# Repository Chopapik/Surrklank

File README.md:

# Surrklank

Surrklank is a local application for an ESP32 device. ASP.NET Core serves the
React interface and communicates with the ESP32 over BLE. The firmware currently
supports connection, ATX control, an FDD Laboratory for up to 12 drives (three FDD modules) and USB/BLE
firmware maintenance. Laboratory motion has been exercised on two physical
FDDs; see the [firmware limits](docs/FIRMWARE.md#fdd-laboratory).

The wiring reference uses **LSM (Lead-Screw Motor)** for the removed optical-drive
stepper motors with lead screws, alongside FDD and HDD. LSM/HDD playback remains
unimplemented; see [instrument names](docs/WIRING.md#instrument-names).

## Run

Install the .NET 10 SDK, Node.js 24 or newer, npm and PlatformIO Core. Build the
frontend before starting ASP.NET:

```sh
npm --prefix frontend ci
npm --prefix frontend run build
python3 run.py
```

On Windows, use `py run.py`. Open <http://127.0.0.1:5173>. `run.py` launches the
C# application; ASP.NET serves `frontend/dist` in the same process. Rider can
also run `backend/Surrklank.csproj` directly. Rebuild the frontend when serving
changed UI files through ASP.NET.

For frontend development, keep ASP.NET running, start
`npm --prefix frontend run dev`, and open <http://127.0.0.1:5174>. Vite forwards
`/api` and `/ws` to ASP.NET. `frontend/dist` and `node_modules` are generated.

The backend uses SimpleSharpBLE 1.2.0. Its packaged native libraries support
Apple Silicon macOS, Windows x64/ARM64 and Linux x64/ARM64, but not Intel macOS.
macOS needs Bluetooth permission for the application or terminal running the
server; Linux needs BlueZ and D-Bus. Check the library's Business Source License
1.1 before commercial use. The first .NET restore needs NuGet access.

## Use the device

The ESP32 advertises the compatibility name `EM-MIDI-IDF`. The application scans
and connects automatically, including after link loss. **Disconnect** pauses
automatic connection until **Connect** is selected. **Ping** is manual; there is
no heartbeat. Browser connection and firmware status arrive over `/ws`.

The ATX switch requests an explicit ON or OFF state. GPIO19 drives the transistor
and the physical GPIO13 button can also change the request. The displayed state
comes from the ESP32's driven output, not from browser storage or a measured
power rail. An unknown state disables the switch. See [wiring](docs/WIRING.md).
ATX ON needs the remote panel connected when the ESP32 starts; otherwise the
app shows that the panel is not connected or not responding. The panel's STOP
button stops every drive even without the app.
The ATX section also shows PWR_OK, the supply's own rail-good signal, and
alerts while ATX is ON without it; the modules stay disconnected until PWR_OK
returns. It lists each actuator module as responding, not responding or
reporting a DRV8833 fault (over-current or over-temperature, not a missing
motor).

**Linie SELECT napędów** sets the select line of each FDD: DS1 for typical PC
drives, DS0 for Amiga drives. The ESP32 stores it and the fields are disabled
while anything plays. The bring-up chain test has no UI control; see
[FIRMWARE.md](docs/FIRMWARE.md#bring-up-chain-test).

The FDD Laboratory selects one or several drives, frequency and playing time.
A batch starts only after every selected drive passes its TRACK0 check.
At 200 Hz and above, the high-rate firmware profile ramps once at tone start
and allows a longer direction-change pause. The mean step rate over the whole
tone is lower than the setting. See the [motion profile](docs/FIRMWARE.md#fdd-laboratory)
when interpreting measurements.
Separate batches can overlap; **Stop FDD** stops one drive and **Stop all**
stops all drives, including preparation. Both finish by parking at TRACK0.
When duration expires, the head stays in place (`stopped`). The next start homes
and checks it before playing again. Live states and telemetry arrive over the
same `/ws`. Stop and wait for parking
before switching ATX off or uploading firmware. The physical ATX button is
ignored while Laboratory owns the drives.

Timing-capable firmware also retains a bounded FDD event history with ESP32
monotonic timestamps. Integrations can query clock correspondence and replay
history through the [timing API](docs/BLE-PROTOCOL.md#laboratory-timing-v1).
Timestamp precision is not independently validated synchronization accuracy.

## Firmware maintenance

Isolate the ESP32 before an upload: USB only, with ATX and register/instrument
wiring disconnected. The interface asks for this confirmation. USB provisioning
requires selecting the connected CP2102 port; BLE OTA transfers only the
application image. The application builds from the current `firmware/` sources.
Neither mode changes eFuses or flash security settings.

Maintenance blocks conflicting device controls. An upload request returns HTTP
202 when the job starts; completion or failure is reported over `/ws`. A busy
device returns HTTP 409 with a reason. If the flash outcome cannot be confirmed,
the job is `uncertain` and does not resend the image automatically. Closing the
browser does not cancel an upload. See [firmware operation](docs/FIRMWARE.md).

## Interfaces and checks

| Interface | Purpose |
| --- | --- |
| `GET /` | React interface |
| `GET /api/connection` | Current connection and firmware snapshot |
| `GET /api/connection/events?limit=10` | Recent connection events |
| `PUT /api/atx` | Explicit `{"state":"on"}` or `{"state":"off"}` request |
| `POST /api/laboratory/play` | Prepare and start a `devices` batch |
| `POST /api/laboratory/stop` | Stop and park one FDD |
| `POST /api/laboratory/stop/all` | Stop and park all FDDs |
| `GET /api/firmware/ports` | Available CP2102 ports |
| `POST /api/firmware/usb`, `POST /api/firmware/ota` | Start a firmware job |
| `WS /ws` | `state` / `laboratory` snapshots and connection actions |

Firmware requests require `{"isolatedHardwareConfirmed":true}`; USB also needs
`"port":"<selected CP2102 port>"`. Local-origin checks apply to mutating HTTP
requests and browser WebSockets. See [application architecture](docs/ARCHITECTURE.md)
and [BLE application protocol](docs/BLE-PROTOCOL.md) for the state flow.

Offline checks:

```sh
dotnet build backend/Surrklank.csproj
npm --prefix frontend run build
npm --prefix frontend test
python3 backend/checks/test_device_state.py
python3 firmware/tests/test_atx_power.py
python3 firmware/tests/test_fdd.py
pio run -d firmware -e esp32
```

The backend check compiles the production state decoder in a temporary .NET
harness; the ATX check compiles the production C++ module with GPIO/FreeRTOS
stubs. The FDD check exercises the production scheduling engine with simulated
TRACK0 and movement, including unequal outward/return movement. These checks
and builds do not exercise a physical ESP32. No C# test
suite for the orchestration layer is included.

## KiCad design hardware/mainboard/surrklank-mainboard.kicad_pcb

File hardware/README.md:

# Surrklank PCB design

Status: **proposed design, not built or tested.** Signals, pins, pull
resistors and power wiring of the planned boards are defined in
[WIRING.md](../docs/WIRING.md); this file covers board-level design only.
Firmware drives three FDD modules (12 drives) and keeps the actuator branch cleared; see
[FIRMWARE.md](../docs/FIRMWARE.md#fdd-laboratory).

KiCad 10 projects:

| Folder | Content |
| --- | --- |
| `fdd-module/` | FDD module v0.1: generated schematic and autorouted 100 × 80 mm 2-layer PCB |
| `actuator-module/` | actuator module v0.1: generated schematic and autorouted 120 × 80 mm 2-layer PCB |
| `mainboard/` | Mainboard v0.1: generated schematic and autorouted 100 × 80 mm 2-layer PCB (within the 100 × 100 mm low-cost fab class) |
| `panel/` | Remote panel v0.1: generated schematic and autorouted 100 × 59 mm 2-layer PCB |
| `surrklank-controller/` | Empty first KiCad project, superseded by `mainboard/` |
| `lib/` | Custom symbols (DRV8833 module, ESP32 38-pin board) and footprints (KF301 screw terminals, ESP32 board, DRV8833 module, Surrklank logo) |
| `tools/` | Generators, netlist check and build script |

Boards are generated, not edited by hand. One command rebuilds a board
(schematic, ERC, netlist check, placement, autorouting, zone fill, DRC with
schematic parity and all severities):

```sh
hardware/tools/build_fdd_module.sh [work_dir]
hardware/tools/build_actuator_module.sh [work_dir]
hardware/tools/build_mainboard.sh [work_dir]
hardware/tools/build_panel.sh [work_dir]
```

All wrap `build_module.sh fdd|actuator|mainboard|panel`, which stops at the first
failing step. Placement, zones and branding of all boards live in
`gen_module_pcb.py`.

Requirements: KiCad 10 (its bundled Python runs `gen_module_pcb.py`), Freerouting
2.5.0 jar in `~/.local/share/freerouting/bin/` (official GitHub release,
SHA-256 `f6f51bb0…5de3c7`) and Java 25 (`brew install openjdk@25`). The script
runs Freerouting headless with analytics and telemetry disabled. The native
Freerouting 2.5.0 CLI build fails on board serialization and is not used.

- `check_fdd_module.py`, `check_actuator_module.py`, `check_mainboard.py` and
  `check_panel.py` verify the netlist against WIRING.md rules written
  independently of the generator (drive header pins, pull-ups, register chain,
  ribbon, supplies).
- Routing is not deterministic: each run gives different tracks, and a run
  occasionally leaves a connection unrouted; rerun the build then. The build
  passes only with zero DRC violations and zero unconnected pads.
- Design rules: Default class 0.25 mm tracks / 0.2 mm clearance, Power class
  (+5V, +3V3, GND) 0.6 mm / 0.25 mm, vias 0.6/0.3 mm, minimum track 0.15 mm
  (above the 0.127 mm limit of low-cost fabs). Freerouting neck-down is disabled;
  any remaining track under 0.15 mm is widened and re-checked by DRC.
- GND is poured on both layers with solid pad connections; dense IDE header
  pins left no room for thermal spokes.
- Actuator module load supply: a +5V band on B_Cu (7.9 mm at its widest, 4.7 mm at the
  four GND notches, about 10 A at +20 K for 1 oz copper by an IPC-2221 estimate;
  the terminal and the PSU wire limit first, so consider 2 oz copper) runs from the two +5V
  poles of KF301 J5 past C8 (+) and the VCC pins of all four DRV8833 slots. Below it
  B_Cu is a solid GND plane reaching each slot's GND pin through a notch in the
  band, plus the two GND poles of J5 and C8 (−). Both zones are passed to Freerouting
  as planes, and a rule area forbids B_Cu tracks and vias there, so signals
  cross on F_Cu only. The band's current capacity for the theoretical 9.6 A is
  estimated, not calculated or measured; the LDO is fed by a 0.6 mm track.
- The autorouted layout is electrically complete but not hand-optimised
  (long detours, signals near edges). It has not been reviewed for signal
  integrity or checked with a 1:1 paper print.

## Board family

| Board | Contents |
| --- | --- |
| Mainboard | ESP32 board, ATX switch and button, PWR_OK input, 5VSB supply, one ribbon connector per branch, remote panel connector |
| FDD module | 3 × 74HC595, 1 × 74HC165, input buffer, LDO, two 40-pin IDE headers, IN/OUT ribbon connectors, one 2-pole KF301 |
| actuator module | Four DRV8833 module positions, 3 × 74HC595, 1 × 74HC165, input buffer, LDO, IN/OUT ribbon connectors, one 4-pole KF301 |

At least two module designs are needed. Whether the mainboard is a third design
or is merged into one of them is not decided.

## Mainboard

ESP32 board as purchased: "ESP32-WROOM-32 38-pin, micro-USB, CP2102"
(seller code ARD-ESP32-38P), about 55.3 × 28 mm, 2 × 19 pins on 2.54 mm pitch,
pin order listed by the seller and matching the silkscreen photo.

- Row spacing is **24.85 mm** centre to centre (many official DevKitC boards
  and 38-pin clones differ: 25.4 and 22.86 mm also occur). Measured by the user
  with a caliper: 25.5 mm across the rows on pin outer edges (minus the 0.64 mm
  pin width) and 24.8 to 24.9 mm directly centre to centre; along a row 46.0 mm
  across 18 pitches (45.72 mm nominal). An earlier footprint used 25.4 mm and
  did not fit a paper dry fit.
- The board plugs into two 1 × 19 female headers on the left of the PCB. Its
  antenna end is flush with the top edge and the top 3.6 mm under it carries
  no copper on either layer (Surrklank uses BLE). It does not overhang: the
  body outline in the footprint is approximate, so the antenna position on
  the real board is not checked.
- Below the USB end the PCB is left free (only the silkscreen note
  "REMOVE JP1 BEFORE USB") so the micro-USB plug clears the ATX terminal (KF301 J1, x 37-58 mm, y 66-74 mm).
- PCB v0.1 layout: register control resistor arrays in the middle, ribbon
  J2 (FDD) and J3 (actuator module) on the right edge, ATX terminal J1 (KF301, 4 poles) at the bottom
  edge with the wire entry outward and labelled poles above it, button J4 bottom right, remote panel
  connector J6 (2 × 5 IDC, see WIRING.md) at the top edge. Autorouted, not
  hand-optimised.
- Power input: KF301 screw terminal on every board that takes power (mainboard 4 poles,
  FDD module 2, actuator module 4); ATX button on a two-pin connector.

## Remote panel

Front panel on a cable to mainboard J6 (pinout in WIRING.md). PCB v0.1,
everything on the front side:

- J1 cable header top left; socket J4 for a 0.96" SSD1306 OLED module (the
  module's 27 × 27 mm body covers the area below the socket, which carries
  only tracks); four 3 mm LEDs top right: STBY and RAILS (hardware), ATX ON
  and ESP (firmware via the expander).
- MCP23017 expander (address 0x20) with 330 Ω LED resistors; 6 mm tactile
  buttons POWER (straight to GPIO13), PREV, PLAY, STOP, NEXT (expander GPA0–3).
- J2 (JST-XH 6-pin): +3V3, GND and GPA4–GPA7 (GPA7 is output only, so three
  more buttons); J3
  (JST-XH 4-pin): I2C extension (GND, VCC, SCL, SDA) for another expander or
  sensor. Keyed JST-XH as on the actuator module outputs, at the bottom edge. GPB2–GPB7 are unused: routing
  them to a header blocked the autorouter.
- All panel nets use the Default 0.25 mm class; the panel draws tens of mA
  and GND is poured on both layers. With 0.6 mm Power tracks Freerouting
  could not route GND between the expander and header pins and left +3V3
  unrouted as well.
- Not decided: mounting in an enclosure, front-panel cutouts, LED colours
  (Vf about 2 V needed for the hardware LEDs).

## Connectors and footprints

| Part | Footprint |
| --- | --- |
| Ribbon IN/OUT | 2 × 8 IDC box header, 2.54 mm |
| FDD drive cable | Salvaged 40-pin IDE header; standard DIN 41651 2 × 20 footprint (2.54 mm pitch, 1.0 mm holes, body about 58.5 × 8.9 mm in KiCad) with extra clearance for a cut-down housing |
| Power input | Custom `TerminalBlock_KF301_1xNN_P5.08mm_Horizontal` (2 and 4 poles, from `gen_terminal_footprints.py`): 5.08 mm pitch, 3.0 mm pads, 1.4 mm holes, generic body about 8 mm deep with the wires entering from the +y side; check against the bought part |
| DRV8833 module | Custom `DRV8833_Module_2x6_W15.24mm`: 2 × 6, 2.54 mm pitch, rows 15.24 mm apart, 1.0 mm holes, DIP-style numbering |
| Motor outputs | JST-XH 4-pin vertical (B4B-XH-A, 2.5 mm) per DRV8833 slot; crimped plugs |
| Actuator module bulk capacitor | 470 µF 16 V radial THT, 10 mm diameter, 5 mm pitch |
| ESP32 board | Two 1 × 19 female headers, 2.54 mm pitch, rows 24.85 mm apart |

Salvaged male Molex headers turned out to be SMD, so every power input is a
KF301 screw terminal (see WIRING.md, Power). A cut-off IDE part can still serve
as an FDD module header.

## Layout notes

- Silkscreen branding, white, board-only footprints (not in the schematic):
  the Surrklank mark (10 mm frame with the beamed-notes glyph, 55 % of the frame
  height, footprint `Surrklank_Mark_10mm` from `gen_logo_footprints.py`) with the
  wordmark "Surrklank" and the board name and revision below it, and the author
  mark (8 mm square ring, `Surrklank_Logo_8mm`) with a small italic "by" in its
  upper-left corner. The author mark is on the back of every board, the front
  carries only the Surrklank mark.
  `gen_module_pcb.py <board> brand` re-applies them without rerouting. Wordmark
  and "by" are TrueType text (Arial bold, Georgia bold italic) outlined in the
  Gerbers; a different font on another machine changes their shape.
- actuator module: ribbon IN/OUT on the left and right edges, registers in a
  row above four DRV8833 slots (rotated so OUT1–OUT4 face the bottom edge),
  JST-XH motor connectors at the bottom edge, 4-pole KF301 J5 at the left edge
  with C8 beside it. Every pole is labelled with its function (+5V or GND) to
  the right of the terminal body. The board is 120 mm wide: C8 and four 18.6 mm
  slots do not fit in 100 mm.
- Ribbon signals keep the signal/ground order of the 16-pin assignment.
- Both modules carry bring-up aids: LEDs D1-D5 (register serial outputs, 165
  return, 3.3 V) at the registers and header J11 (3V3, DATA, CLK, LATCH, end of
  chain, GND). The FDD module stays 100 x 80 mm, within the 100 x 100 mm limit.

## Manufacturing

There is no factory assembly: bare boards are ordered and every part is bought
separately and soldered by hand (SOIC, 0603 and SOT-223 included). The BOM
written by `export_jlcpcb.py` doubles as a shopping list.

`hardware/tools/export_review.py [board ...]` writes review tables to
`hardware/fabrication/review/` (git-ignored): a pin-by-pin table per board from
the netlist (connectors, modules, switches, LEDs: pin name, net, what else is
on it). The tables are generated from the schematic, so they are the thing to
compare with the real parts and breadboard wiring; `check_*.py` only compares
the schematic with WIRING.md.

`hardware/tools/export_dryfit.py` (run with KiCad's Python, which provides
`pcbnew`) writes `surrklank-dryfit-a4-1to1.pdf` to the same folder: one A4
landscape sheet with all four boards at true size for a paper dry fit. Black
lines are the board edge, footprint outlines and mounting holes; red circles
are through-hole pads with their drills; tracks and SMD parts are left out to
save ink. A 10 cm ruler along both axes shows whether the printer rescaled the
page: print at 100 % / actual size, never fit to page.

`hardware/tools/export_jlcpcb.py [board ...]` writes upload files to
`hardware/fabrication/` (git-ignored): one Gerber and drill zip per board
(separate PTH and NPTH files, paste layers included), plus an SMD BOM (`bom/`) and CPL (`cpl/`)
that are only needed if factory assembly is used. The BOM carries only
LCSC numbers whose JLCPCB class was read as Basic or Promotional (Preferred)
Extended on 2026-11-15 (class and stock change, recheck before ordering);
the only Promotional part is the 74HC165 (C5613), which is free of the
loading fee in Economic assembly only. Four part types have no Basic or
Promotional option and stay without a number, listed in `UNRESOLVED` in the
script with their Extended candidates (extra fee per unique part type):
74LVC244A (SOIC-20W) on both modules, the 33 Ω 0603 × 4 array (mainboard and
both modules), the 100 k 0603 × 4 array (actuator module) and the panel's
MCP23017-E/SO. These parts are left out of the assembly BOM and CPL and listed
in `bom/surrklank-<board>-hand-solder.csv`: the factory places only Basic and
Promotional parts and these are soldered by hand. CPL rotation offsets are verified only for
SOIC-16/20 and SOT-223; SOT-23, resistor arrays and SOIC-28W must be checked
in the JLCPCB placement preview.

## Open items

- Before ordering: dry-fit the 1:1 sheet (`export_dryfit.py`) with the real ESP32
  board, salvaged IDE header, KF301 terminals, buttons and OLED; measure the
  DRV8833 module J1 and EEP pull-up supply with a multimeter.
- Parts: AMS1117 with the 22 µF 1206 ceramic is untested (datasheet silent on
  ceramics; scope the 3.3 V rail of the first module).
- Power input: KF301 pole and body size against the bought terminals (generic values in the footprints).
- MOTOR behaviour on the installed drives (the hand-wired assembly works with
  TRACK0 pulled up and no 595 output pull-ups).
- Motor supply current per actuator module and wire gauge.
- Firmware migration after assembly: six outputs per drive and a longer FDD
  chain (48 output bits for two modules), 165 chains with WRITE PROTECT and
  FAULT bits, configurable select line, EEP control, PWR_OK input on GPIO36,
  actuator Q165 on GPIO35, DATA, CLK, LATCH and CLK165 held LOW (and /OE and
  /PL HIGH) while ATX is off.

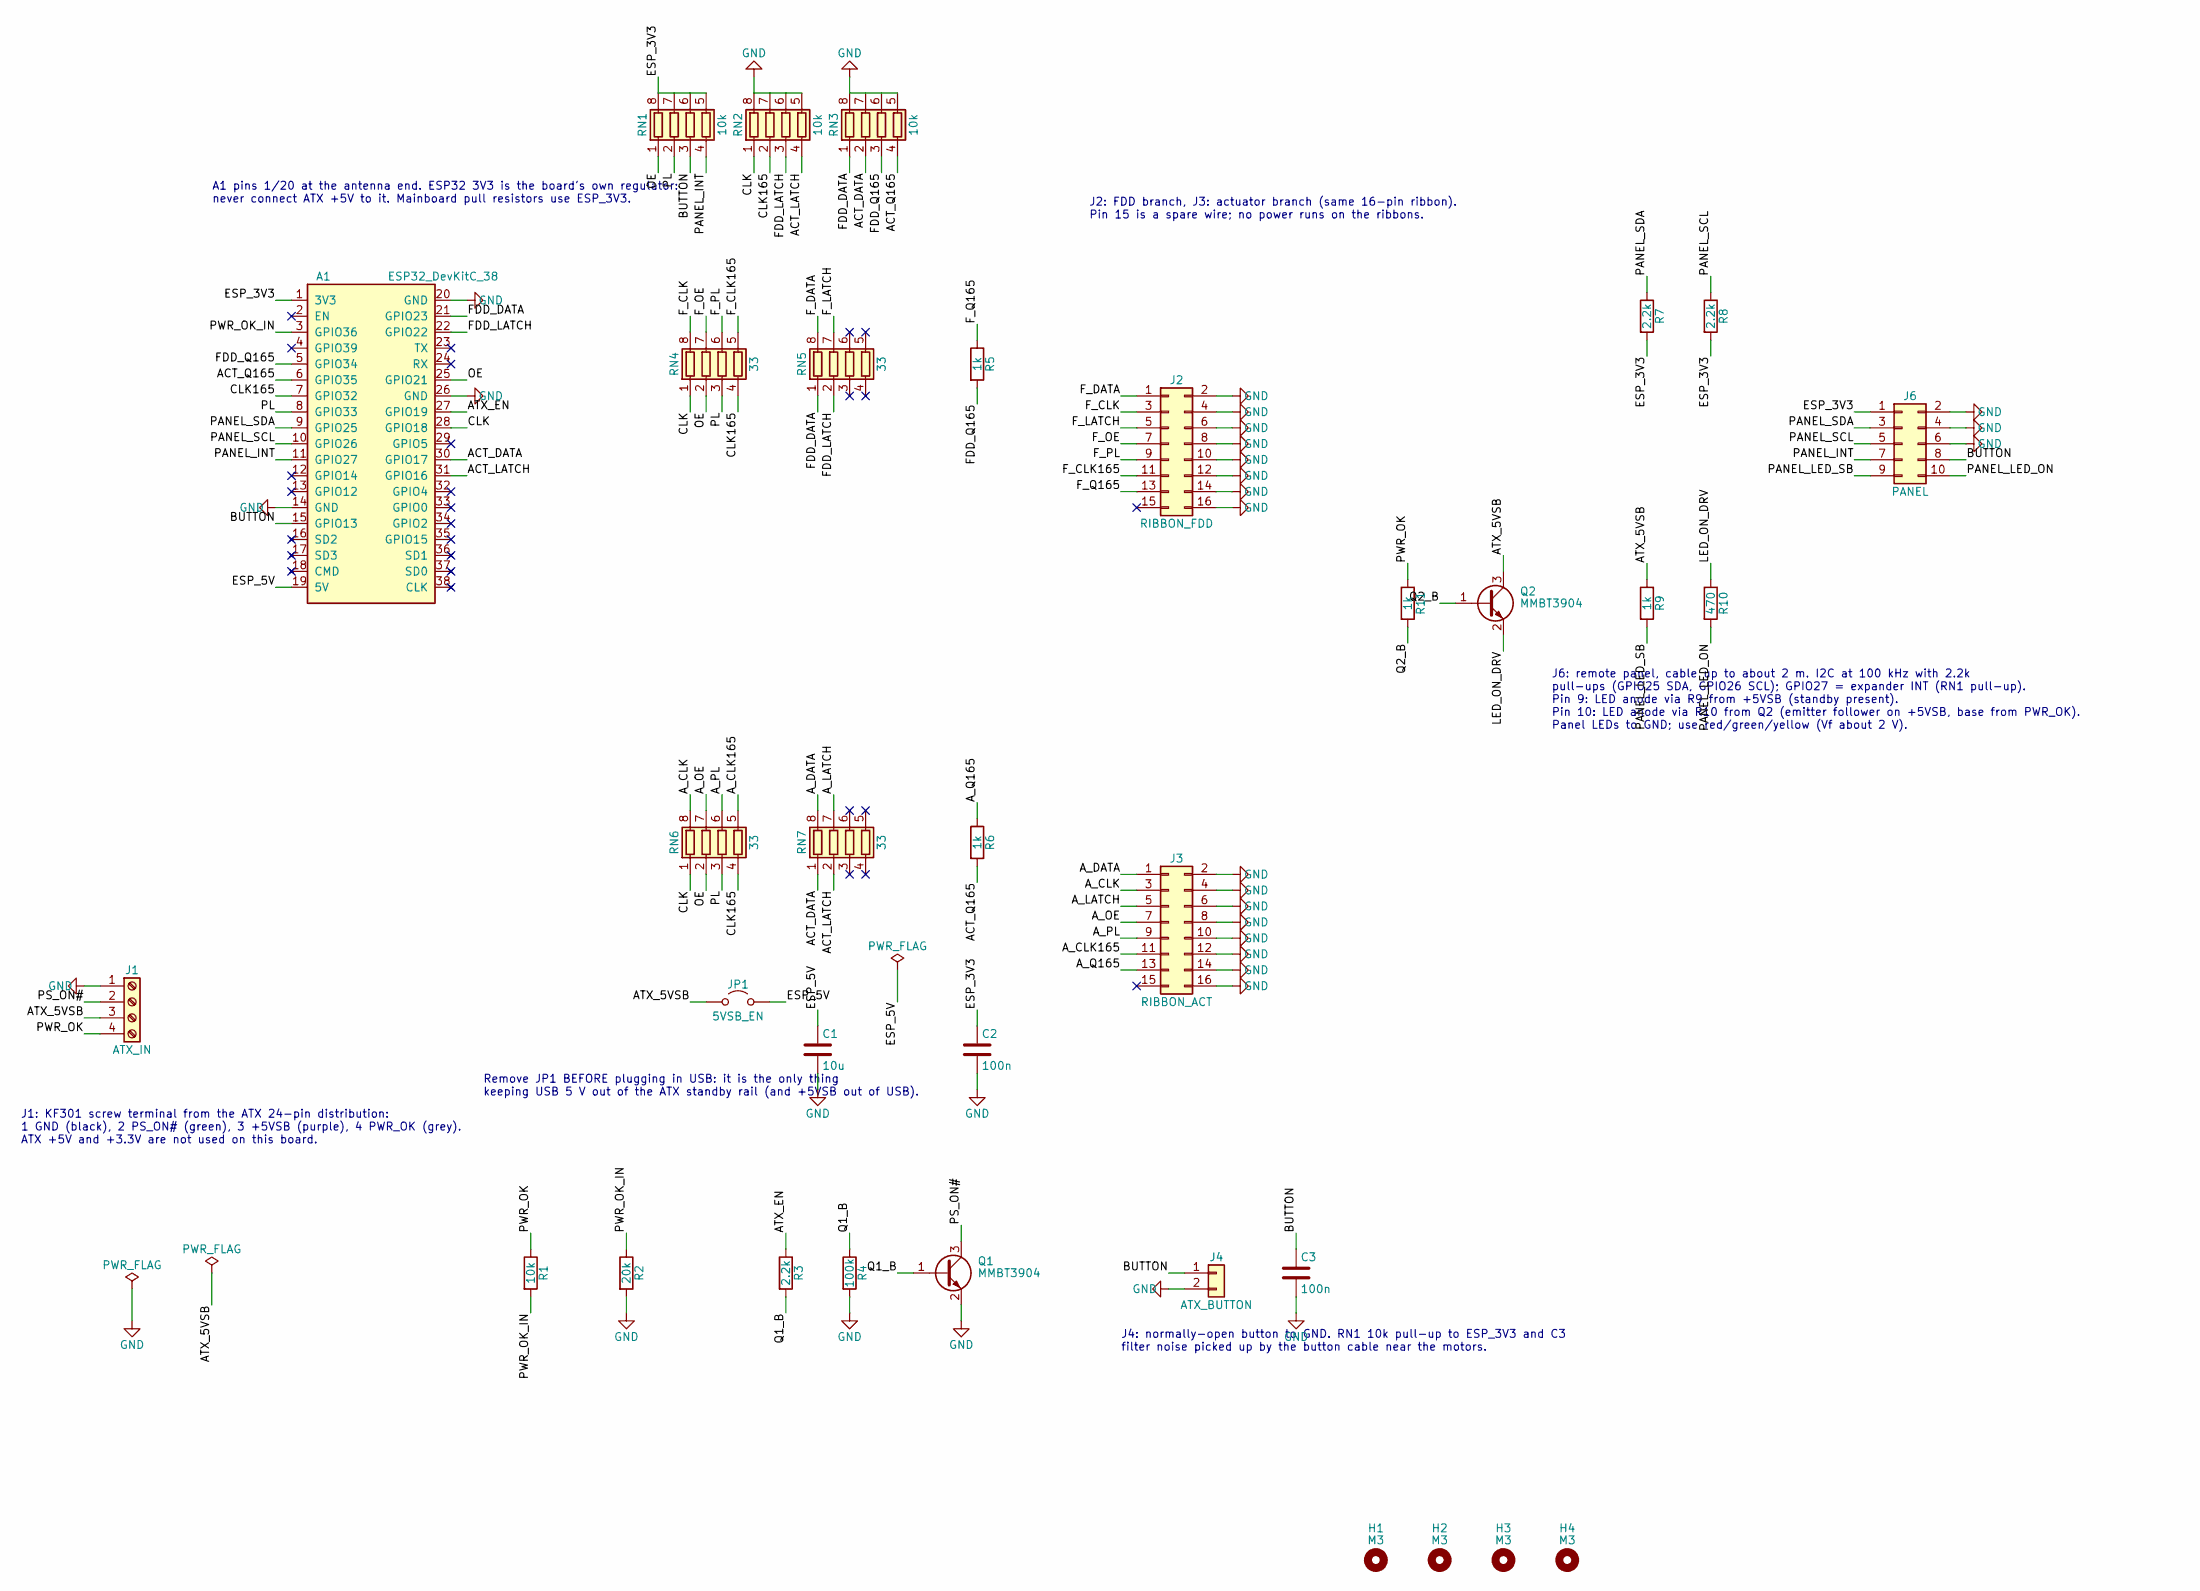
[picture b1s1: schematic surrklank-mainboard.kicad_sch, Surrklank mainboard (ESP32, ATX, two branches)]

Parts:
A1: ESP32_DevKitC_38; ESP32_DevKitC_38_W24.85mm
C1: 10u; C_0805_2012Metric
C2, C3: 100n; C_0805_2012Metric
H1, H2, H3, H4: M3; MountingHole_3.2mm_M3
J1: ATX_IN; TerminalBlock_KF301_1x04_P5.08mm_Horizontal
J2: RIBBON_FDD; IDC-Header_2x08_P2.54mm_Vertical
J3: RIBBON_ACT; IDC-Header_2x08_P2.54mm_Vertical
J4: ATX_BUTTON; JST_XH_B2B-XH-A_1x02_P2.50mm_Vertical
J6: PANEL; IDC-Header_2x05_P2.54mm_Vertical
JP1: 5VSB_EN; PinHeader_1x02_P2.54mm_Vertical
Q1, Q2: MMBT3904; SOT-23
R1: 10k; R_0805_2012Metric
R2: 20k; R_0805_2012Metric
R3, R7, R8: 2.2k; R_0805_2012Metric
R4: 100k; R_0805_2012Metric
R5, R6, R9, R11: 1k; R_0805_2012Metric
R10: 470; R_0805_2012Metric
RN1, RN2, RN3: 10k; R_Array_Convex_4x0603
RN4, RN5, RN6, RN7: 33; R_Array_Convex_4x0603

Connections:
/ACT_DATA: A1.30 (GPIO17), RN3.2 (R2.1), RN7.1 (R1.1)
/ACT_LATCH: A1.31 (GPIO16), RN2.4 (R4.1), RN7.2 (R2.1)
/ACT_Q165: A1.6 (GPIO35), R6.2, RN3.4 (R4.1)
/ATX_5VSB: J1.3, JP1.1 (A), Q2.3 (C), R9.1
/ATX_EN: A1.27 (GPIO19), R3.1
/A_CLK: J3.3, RN6.8 (R1.2)
/A_CLK165: J3.11, RN6.5 (R4.2)
/A_DATA: J3.1, RN7.8 (R1.2)
/A_LATCH: J3.5, RN7.7 (R2.2)
/A_OE: J3.7, RN6.7 (R2.2)
/A_PL: J3.9, RN6.6 (R3.2)
/A_Q165: J3.13, R6.1
/BUTTON: A1.15 (GPIO13), C3.1, J4.1, J6.8, RN1.3 (R3.1)
/CLK: A1.28 (GPIO18), RN2.1 (R1.1), RN4.1 (R1.1), RN6.1 (R1.1)
/CLK165: A1.7 (GPIO32), RN2.2 (R2.1), RN4.4 (R4.1), RN6.4 (R4.1)
/ESP_3V3: A1.1 (3V3), C2.1, J6.1, R7.2, R8.2, RN1.5 (R4.2), RN1.6 (R3.2), RN1.7 (R2.2), RN1.8 (R1.2)
/ESP_5V: A1.19 (5V), C1.1, JP1.2 (B)
/FDD_DATA: A1.21 (GPIO23), RN3.1 (R1.1), RN5.1 (R1.1)
/FDD_LATCH: A1.22 (GPIO22), RN2.3 (R3.1), RN5.2 (R2.1)
/FDD_Q165: A1.5 (GPIO34), R5.2, RN3.3 (R3.1)
/F_CLK: J2.3, RN4.8 (R1.2)
/F_CLK165: J2.11, RN4.5 (R4.2)
/F_DATA: J2.1, RN5.8 (R1.2)
/F_LATCH: J2.5, RN5.7 (R2.2)
/F_OE: J2.7, RN4.7 (R2.2)
/F_PL: J2.9, RN4.6 (R3.2)
/F_Q165: J2.13, R5.1
/LED_ON_DRV: Q2.2 (E), R10.1
/OE: A1.25 (GPIO21), RN1.1 (R1.1), RN4.2 (R2.1), RN6.2 (R2.1)
/PANEL_INT: A1.11 (GPIO27), J6.7, RN1.4 (R4.1)
/PANEL_LED_ON: J6.10, R10.2
/PANEL_LED_SB: J6.9, R9.2
/PANEL_SCL: A1.10 (GPIO26), J6.5, R8.1
/PANEL_SDA: A1.9 (GPIO25), J6.3, R7.1
/PL: A1.8 (GPIO33), RN1.2 (R2.1), RN4.3 (R3.1), RN6.3 (R3.1)
/PS_ON#: J1.2, Q1.3 (C)
/PWR_OK: J1.4, R1.1, R11.1
/PWR_OK_IN: A1.3 (GPIO36), R1.2, R2.1
/Q1_B: Q1.1 (B), R3.2, R4.1
/Q2_B: Q2.1 (B), R11.2
GND: A1.14 (GND), A1.20 (GND), A1.26 (GND), C1.2, C2.2, C3.2, J1.1, J2.2, J2.4, J2.6, J2.8, J2.10, J2.12, J2.14, J2.16, J3.2, J3.4, J3.6, J3.8, J3.10, J3.12, J3.14, J3.16, J4.2, J6.2, J6.4, J6.6, Q1.2 (E), R2.2, R4.2, RN2.5 (R4.2), RN2.6 (R3.2), RN2.7 (R2.2), RN2.8 (R1.2), RN3.5 (R4.2), RN3.6 (R3.2), RN3.7 (R2.2), RN3.8 (R1.2)

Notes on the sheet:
A1 pins 1/20 at the antenna end. ESP32 3V3 is the board's own regulator: never connect ATX +5V to it. Mainboard pull resistors use ESP_3V3.
J2: FDD branch, J3: actuator branch (same 16-pin ribbon). Pin 15 is a spare wire; no power runs on the ribbons.
J1: KF301 screw terminal from the ATX 24-pin distribution: 1 GND (black), 2 PS_ON# (green), 3 +5VSB (purple), 4 PWR_OK (grey). ATX +5V and +3.3V are not used on this board.
Remove JP1 BEFORE plugging in USB: it is the only thing keeping USB 5 V out of the ATX standby rail (and +5VSB out of USB).
J4: normally-open button to GND. RN1 10k pull-up to ESP_3V3 and C3 filter noise picked up by the button cable near the motors.
J6: remote panel, cable up to about 2 m. I2C at 100 kHz with 2.2k pull-ups (GPIO25 SDA, GPIO26 SCL); GPIO27 = expander INT (RN1 pull-up). Pin 9: LED anode via R9 from +5VSB (standby present). Pin 10: LED anode via R10 from Q2 (emitter follower on +5VSB, base from PWR_OK). Panel LEDs to GND; use red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

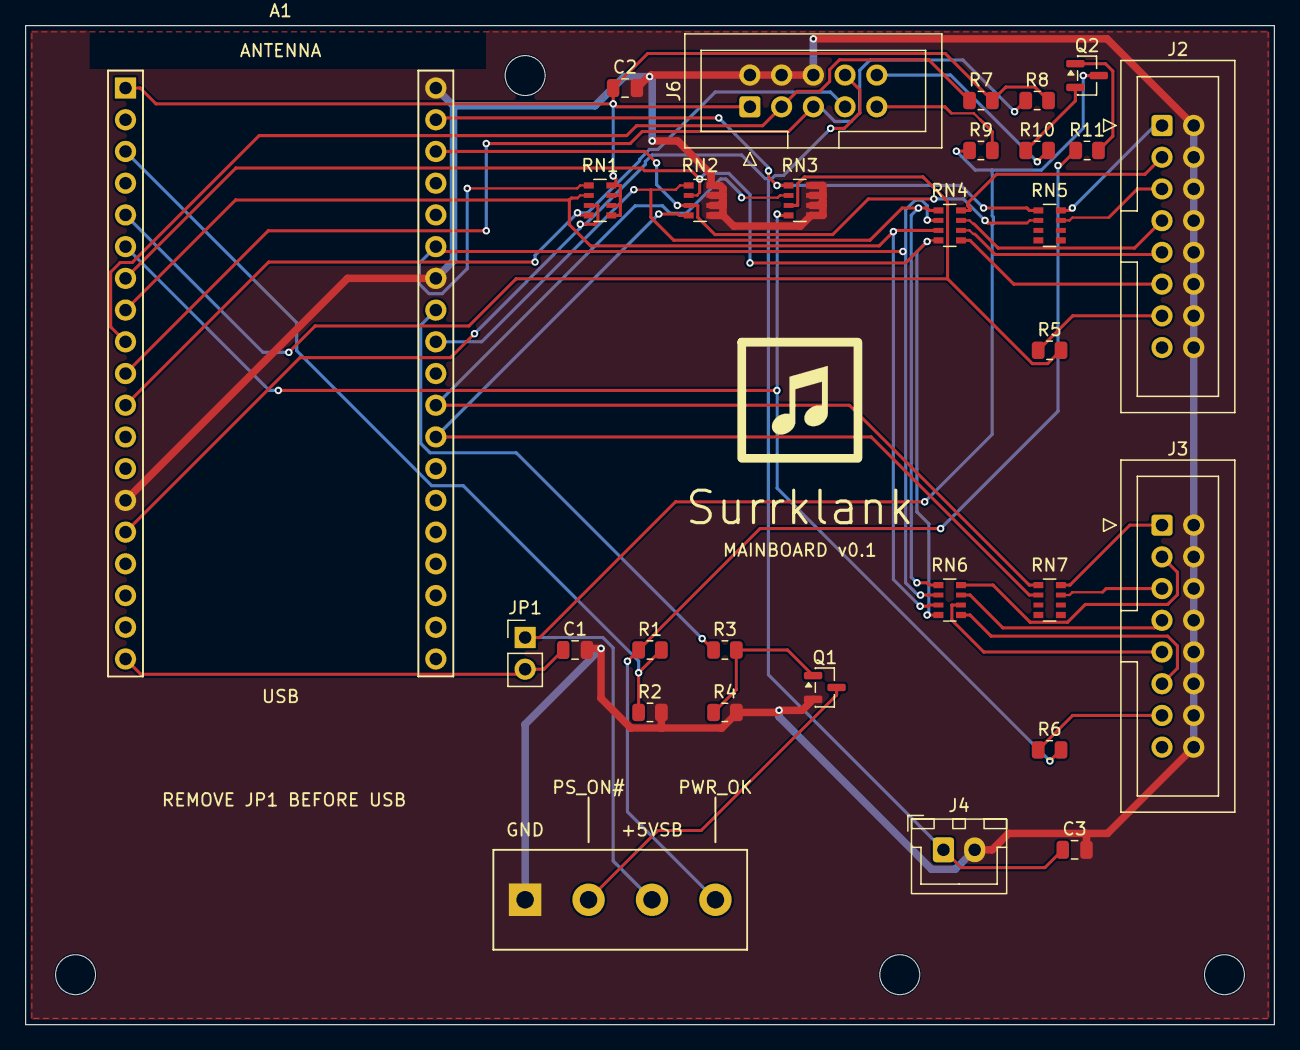
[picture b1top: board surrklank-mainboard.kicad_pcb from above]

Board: 2 copper layers, 100.0 x 80.0 mm, 36 parts (1 on the bottom side), 41 nets.

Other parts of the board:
LOGO1: Surrklank_Logo; Surrklank_Logo_8mm
LOGO2: Surrklank_Mark; Surrklank_Mark_10mm

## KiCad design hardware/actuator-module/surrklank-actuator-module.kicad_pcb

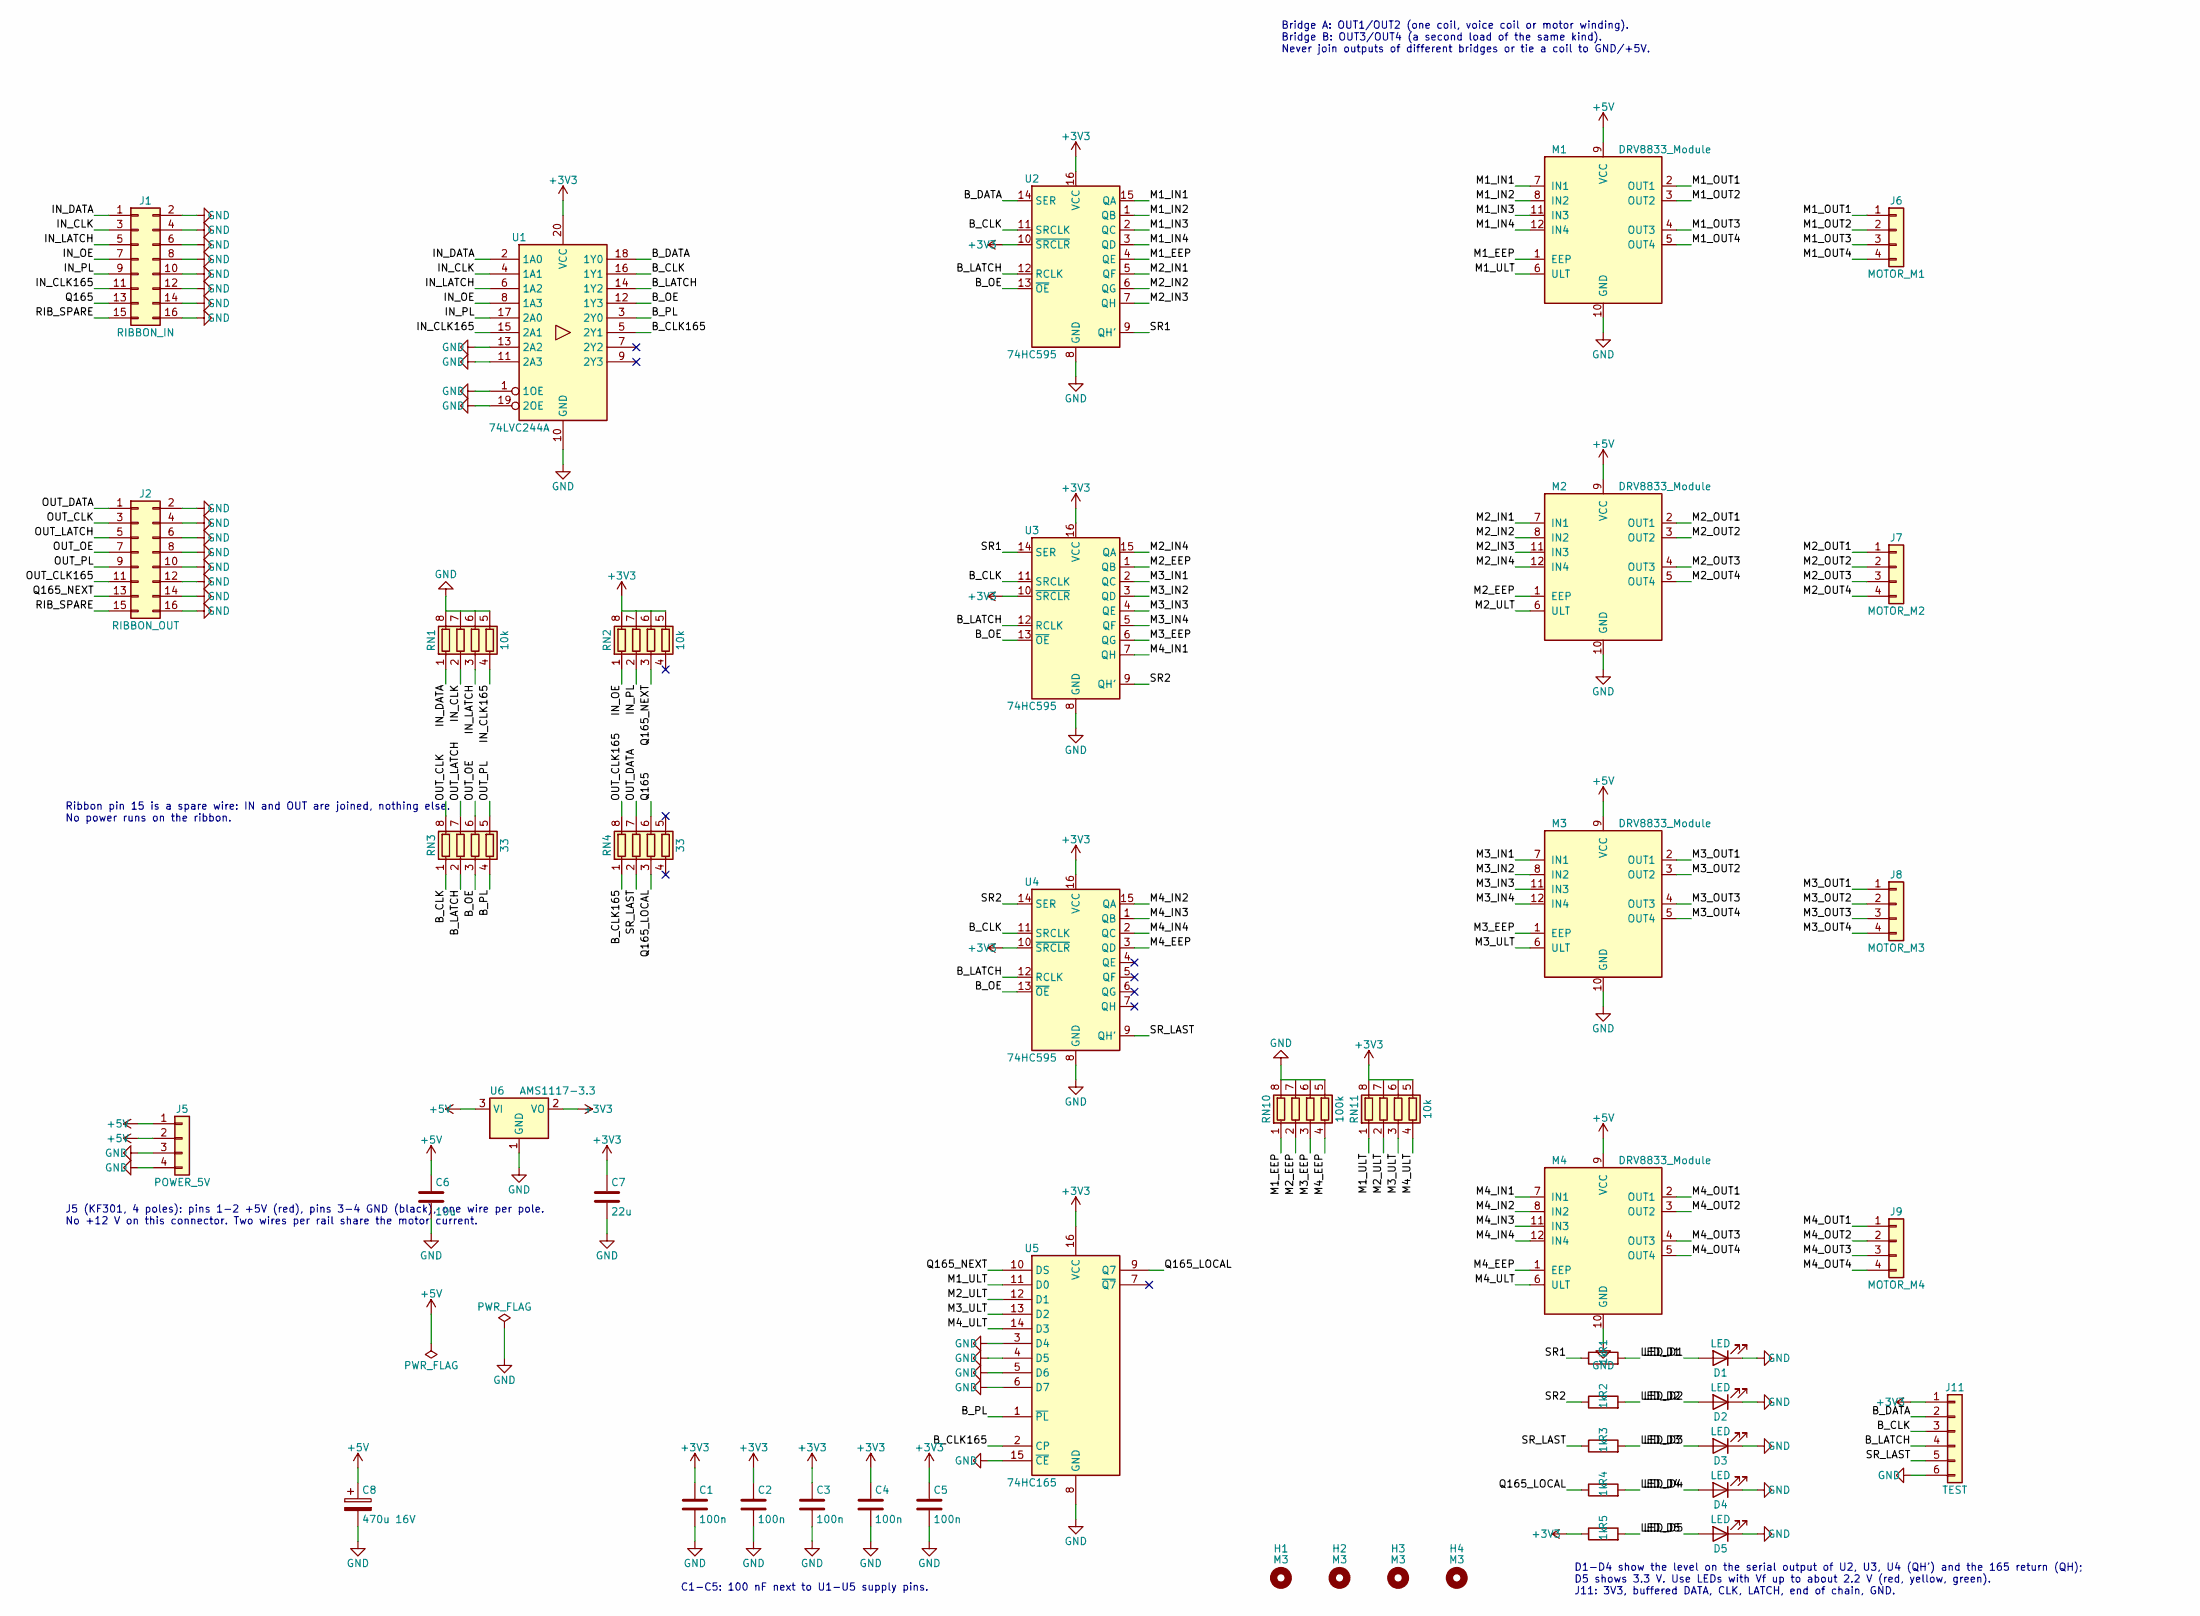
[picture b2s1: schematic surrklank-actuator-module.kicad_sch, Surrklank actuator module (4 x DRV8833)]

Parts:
C1, C2, C3, C4, C5: 100n; C_0805_2012Metric
C6: 10u; C_0805_2012Metric
C7: 22u; C_1206_3216Metric
C8: 470u 16V; CP_Radial_D10.0mm_P5.00mm
D1, D2, D3, D4, D5: LED; LED_0603_1608Metric
H1, H2, H3, H4: M3; MountingHole_3.2mm_M3
J1: RIBBON_IN; IDC-Header_2x08_P2.54mm_Vertical
J2: RIBBON_OUT; IDC-Header_2x08_P2.54mm_Vertical
J5: POWER_5V; TerminalBlock_KF301_1x04_P5.08mm_Horizontal
J6: MOTOR_M1; JST_XH_B4B-XH-A_1x04_P2.50mm_Vertical
J7: MOTOR_M2; JST_XH_B4B-XH-A_1x04_P2.50mm_Vertical
J8: MOTOR_M3; JST_XH_B4B-XH-A_1x04_P2.50mm_Vertical
J9: MOTOR_M4; JST_XH_B4B-XH-A_1x04_P2.50mm_Vertical
J11: TEST; PinHeader_1x06_P2.54mm_Vertical
M1, M2, M3, M4: DRV8833_Module; DRV8833_Module_2x6_W15.24mm
R1, R2, R3, R4, R5: 1k; R_0603_1608Metric
RN1, RN2, RN11: 10k; R_Array_Convex_4x0603
RN3, RN4: 33; R_Array_Convex_4x0603
RN10: 100k; R_Array_Convex_4x0603
U1: 74LVC244A; SOIC-20W_7.5x12.8mm_P1.27mm
U2, U3, U4: 74HC595; SOIC-16_3.9x9.9mm_P1.27mm
U5: 74HC165; SOIC-16_3.9x9.9mm_P1.27mm
U6: AMS1117-3.3; SOT-223-3_TabPin2

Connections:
+3V3: C1.1, C2.1, C3.1, C4.1, C5.1, C7.1, J11.1, R5.1, RN2.5 (R4.2), RN2.6 (R3.2), RN2.7 (R2.2), RN2.8 (R1.2), RN11.5 (R4.2), RN11.6 (R3.2), RN11.7 (R2.2), RN11.8 (R1.2), U1.20 (VCC), U2.10 (~SRCLR), U2.16 (VCC), U3.10 (~SRCLR), U3.16 (VCC), U4.10 (~SRCLR), U4.16 (VCC), U5.16 (VCC), U6.2 (VO)
+5V: C6.1, C8.1, J5.1, J5.2, M1.9 (VCC), M2.9 (VCC), M3.9 (VCC), M4.9 (VCC), U6.3 (VI)
/B_CLK: J11.3, RN3.1 (R1.1), U1.16 (1Y1), U2.11 (SRCLK), U3.11 (SRCLK), U4.11 (SRCLK)
/B_CLK165: RN4.1 (R1.1), U1.5 (2Y1), U5.2 (CP)
/B_DATA: J11.2, U1.18 (1Y0), U2.14 (SER)
/B_LATCH: J11.4, RN3.2 (R2.1), U1.14 (1Y2), U2.12 (RCLK), U3.12 (RCLK), U4.12 (RCLK)
/B_OE: RN3.3 (R3.1), U1.12 (1Y3), U2.13 (~OE), U3.13 (~OE), U4.13 (~OE)
/B_PL: RN3.4 (R4.1), U1.3 (2Y0), U5.1 (~PL)
/IN_CLK: J1.3, RN1.2 (R2.1), U1.4 (1A1)
/IN_CLK165: J1.11, RN1.4 (R4.1), U1.15 (2A1)
/IN_DATA: J1.1, RN1.1 (R1.1), U1.2 (1A0)
/IN_LATCH: J1.5, RN1.3 (R3.1), U1.6 (1A2)
/IN_OE: J1.7, RN2.1 (R1.1), U1.8 (1A3)
/IN_PL: J1.9, RN2.2 (R2.1), U1.17 (2A0)
/LED_D1: D1.2 (A), R1.2
/LED_D2: D2.2 (A), R2.2
/LED_D3: D3.2 (A), R3.2
/LED_D4: D4.2 (A), R4.2
/LED_D5: D5.2 (A), R5.2
/M1_EEP: M1.1 (EEP), RN10.1 (R1.1), U2.4 (QE)
/M1_IN1: M1.7 (IN1), U2.15 (QA)
/M1_IN2: M1.8 (IN2), U2.1 (QB)
/M1_IN3: M1.11 (IN3), U2.2 (QC)
/M1_IN4: M1.12 (IN4), U2.3 (QD)
/M1_OUT1: J6.1, M1.2 (OUT1)
/M1_OUT2: J6.2, M1.3 (OUT2)
/M1_OUT3: J6.3, M1.4 (OUT3)
/M1_OUT4: J6.4, M1.5 (OUT4)
/M1_ULT: M1.6 (ULT), RN11.1 (R1.1), U5.11 (D0)
/M2_EEP: M2.1 (EEP), RN10.2 (R2.1), U3.1 (QB)
/M2_IN1: M2.7 (IN1), U2.5 (QF)
/M2_IN2: M2.8 (IN2), U2.6 (QG)
/M2_IN3: M2.11 (IN3), U2.7 (QH)
/M2_IN4: M2.12 (IN4), U3.15 (QA)
/M2_OUT1: J7.1, M2.2 (OUT1)
/M2_OUT2: J7.2, M2.3 (OUT2)
/M2_OUT3: J7.3, M2.4 (OUT3)
/M2_OUT4: J7.4, M2.5 (OUT4)
/M2_ULT: M2.6 (ULT), RN11.2 (R2.1), U5.12 (D1)
/M3_EEP: M3.1 (EEP), RN10.3 (R3.1), U3.6 (QG)
/M3_IN1: M3.7 (IN1), U3.2 (QC)
/M3_IN2: M3.8 (IN2), U3.3 (QD)
/M3_IN3: M3.11 (IN3), U3.4 (QE)
/M3_IN4: M3.12 (IN4), U3.5 (QF)
/M3_OUT1: J8.1, M3.2 (OUT1)
/M3_OUT2: J8.2, M3.3 (OUT2)
/M3_OUT3: J8.3, M3.4 (OUT3)
/M3_OUT4: J8.4, M3.5 (OUT4)
/M3_ULT: M3.6 (ULT), RN11.3 (R3.1), U5.13 (D2)
/M4_EEP: M4.1 (EEP), RN10.4 (R4.1), U4.3 (QD)
/M4_IN1: M4.7 (IN1), U3.7 (QH)
/M4_IN2: M4.8 (IN2), U4.15 (QA)
/M4_IN3: M4.11 (IN3), U4.1 (QB)
/M4_IN4: M4.12 (IN4), U4.2 (QC)
/M4_OUT1: J9.1, M4.2 (OUT1)
/M4_OUT2: J9.2, M4.3 (OUT2)
/M4_OUT3: J9.3, M4.4 (OUT3)
/M4_OUT4: J9.4, M4.5 (OUT4)
/M4_ULT: M4.6 (ULT), RN11.4 (R4.1), U5.14 (D3)
/OUT_CLK: J2.3, RN3.8 (R1.2)
/OUT_CLK165: J2.11, RN4.8 (R1.2)
/OUT_DATA: J2.1, RN4.7 (R2.2)
/OUT_LATCH: J2.5, RN3.7 (R2.2)
/OUT_OE: J2.7, RN3.6 (R3.2)
/OUT_PL: J2.9, RN3.5 (R4.2)
/Q165: J1.13, RN4.6 (R3.2)
/Q165_LOCAL: R4.1, RN4.3 (R3.1), U5.9 (Q7)
/Q165_NEXT: J2.13, RN2.3 (R3.1), U5.10 (DS)
/RIB_SPARE: J1.15, J2.15
/SR1: R1.1, U2.9 (QH'), U3.14 (SER)
/SR2: R2.1, U3.9 (QH'), U4.14 (SER)
/SR_LAST: J11.5, R3.1, RN4.2 (R2.1), U4.9 (QH')
GND: C1.2, C2.2, C3.2, C4.2, C5.2, C6.2, C7.2, C8.2, D1.1 (K), D2.1 (K), D3.1 (K), D4.1 (K), D5.1 (K), J1.2, J1.4, J1.6, J1.8, J1.10, J1.12, J1.14, J1.16, J2.2, J2.4, J2.6, J2.8, J2.10, J2.12, J2.14, J2.16, J5.3, J5.4, J11.6, M1.10 (GND), M2.10 (GND), M3.10 (GND), M4.10 (GND), RN1.5 (R4.2), RN1.6 (R3.2), RN1.7 (R2.2), RN1.8 (R1.2), RN10.5 (R4.2), RN10.6 (R3.2), RN10.7 (R2.2), RN10.8 (R1.2), U1.1 (1OE), U1.10 (GND), U1.11 (2A3), U1.13 (2A2), U1.19 (2OE), U2.8 (GND), U3.8 (GND), U4.8 (GND), U5.3 (D4), U5.4 (D5), U5.5 (D6), U5.6 (D7), U5.8 (GND), U5.15 (~CE), U6.1 (GND)

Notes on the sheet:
Ribbon pin 15 is a spare wire: IN and OUT are joined, nothing else. No power runs on the ribbon.
Bridge A: OUT1/OUT2 (one coil, voice coil or motor winding). Bridge B: OUT3/OUT4 (a second load of the same kind). Never join outputs of different bridges or tie a coil to GND/+5V.
J5 (KF301, 4 poles): pins 1-2 +5V (red), pins 3-4 GND (black), one wire per pole. No +12 V on this connector. Two wires per rail share the motor current.
C1-C5: 100 nF next to U1-U5 supply pins.
D1-D4 show the level on the serial output of U2, U3, U4 (QH') and the 165 return (QH); D5 shows 3.3 V. Use LEDs with Vf up to about 2.2 V (red, yellow, green). J11: 3V3, buffered DATA, CLK, LATCH, end of chain, GND.

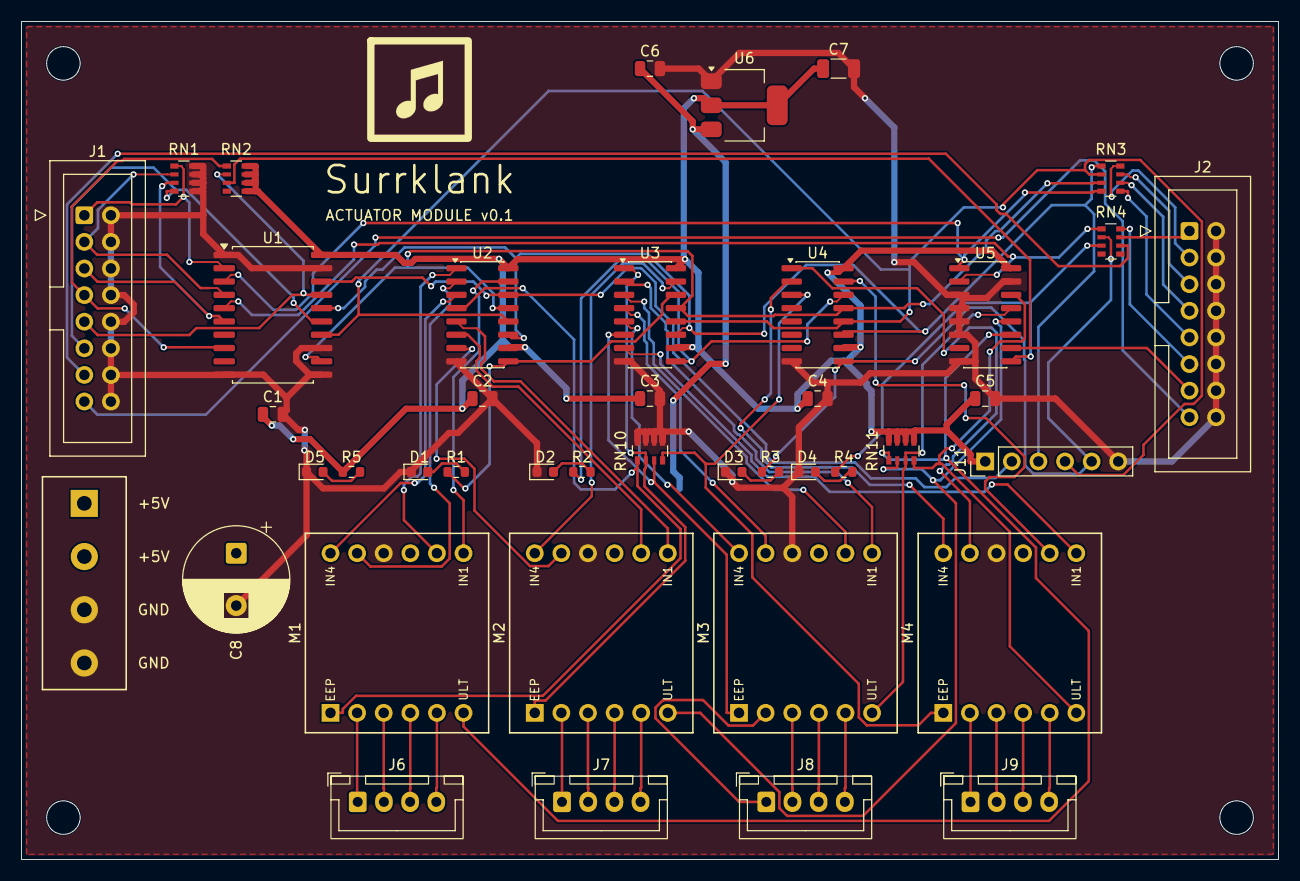
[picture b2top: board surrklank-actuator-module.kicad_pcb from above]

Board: 2 copper layers, 120.0 x 80.0 mm, 48 parts (1 on the bottom side), 73 nets.

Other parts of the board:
LOGO1: Surrklank_Logo; Surrklank_Logo_8mm
LOGO2: Surrklank_Mark; Surrklank_Mark_10mm
